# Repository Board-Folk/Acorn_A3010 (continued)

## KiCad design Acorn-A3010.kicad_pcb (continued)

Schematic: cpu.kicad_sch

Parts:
C84: 10uF 16V; CP_Radial_D4.0mm_P2.00mm
C94, C100, C101, C102, C119: 33nF; C_0805_2012Metric; LCSC C344201
C98, C99, C224: 12pF 2%; C_0805_2012Metric; LCSC C1792
C120: 10uF 10V 20%; CP_Radial_Tantal_D7.0mm_P5.00mm
D19: BAS16; SOT-23
IC8: 74HCT14; SOIC-14_3.9x8.7mm_P1.27mm; LCSC C6769
IC12: DS2401+; TO-92_Inline_Wide
IC13: ARM250; PQFP-160_28x28mm_P0.65mm
IC20: 74HC138; SOIC-16_3.9x9.9mm_P1.27mm; LCSC C5602
IC27: 74AC32; SOIC-14_3.9x8.7mm_P1.27mm; LCSC C352943
R3: 22R; R_0805_2012Metric; LCSC C2907244; not fitted
R50, R115, R124, R219: 68R 5% 0.1W; R_0805_2012Metric; LCSC C137498
R83, R84, R85, R86, R87, R89, R91, R102: 4K7 5% 0.1W; R_0805_2012Metric; LCSC C2907326
R88: 1K0 5% 0.1W; R_0805_2012Metric; LCSC C2907326
R94: 100K 5% 0.1W; R_0805_2012Metric; LCSC C149504
R97: 22R 5% 0.1W; R_0805_2012Metric; LCSC C2907244
R104: 1M0 5% 0.1W; R_0805_2012Metric; LCSC C2933280
R110: 47R 5% 0.1W; R_0805_2012Metric; LCSC C137498
R218: 47R 5% 0.1W; R_0805_2012Metric; LCSC C2907268
R223: 220R 5% 0.1W; R_0805_2012Metric; LCSC C17557
R228, R610, R611, R612: 33R 5% 0.1W; R_0805_2012Metric; LCSC C17634
R608: 33R 5% 0.1W; R_0805_2012Metric
RP7: 68Rx8 5%; SOIC-16W_5.3x10.2mm_P1.27mm; LCSC C1739978
RP11: 68Rx8 5%; SOIC-16W_5.3x10.2mm_P1.27mm
TP4: Test; TestPoint_Pad_D1.0mm; not fitted
TP27: compSync; TestPoint_Pad_D1.0mm; not fitted
TP33: ~{EFiq}; TestPoint_Pad_D1.0mm; not fitted
TP34: C2; TestPoint_Pad_D1.0mm; not fitted
TP35: I13; TestPoint_Pad_D1.0mm; not fitted
X4: 72.0MHz; Oscillator_DIP-14
X5: 25.175MHz; Crystal_HC49-4H_Vertical
X100: 40.0MHz; Oscillator_DIP-14; not fitted

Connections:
+5V: C94.1, C100.1, C101.1, C102.1, C119.1, C120.1, D19.3 (K), IC8.14 (VCC), IC13.10 (Vdd), IC13.29 (Vdd), IC13.50 (Vdd), IC13.68 (Vdd), IC13.90 (Vdd), IC13.108 (Vdd), IC13.127 (Vdd), IC13.147 (Vdd), IC20.6 (E3), IC20.16 (VCC), IC27.14 (VCC), R83.2, R84.2, R85.2, R86.2, R87.2, R88.2, R89.1, R91.1, R94.1, R102.2, X4.1 (EN), X4.14 (Vcc), X100.1 (EN), X100.14 (Vcc); also elsewhere on the board
/CPU/Bd0: RP11.1 (R1.1); also elsewhere on the board
/CPU/Bd1: RP11.2 (R2.1); also elsewhere on the board
/CPU/Bd2: RP11.3 (R3.1); also elsewhere on the board
/CPU/Bd3: RP11.4 (R4.1); also elsewhere on the board
/CPU/Bd4: RP11.5 (R5.1); also elsewhere on the board
/CPU/Bd5: RP11.6 (R6.1); also elsewhere on the board
/CPU/Bd6: RP11.7 (R7.1); also elsewhere on the board
/CPU/Bd7: RP11.8 (R8.1); also elsewhere on the board
/CPU/Cas0: IC13.24 (~Cas0); also elsewhere on the board
/CPU/Cas1: IC13.25 (~Cas1); also elsewhere on the board
/CPU/Cas2: IC13.26 (~Cas2); also elsewhere on the board
/CPU/Cas3: IC13.27 (~Cas3); also elsewhere on the board
/CPU/D0: IC13.41 (D0); also elsewhere on the board
/CPU/D1: IC13.42 (D1); also elsewhere on the board
/CPU/D2: IC13.43 (D2); also elsewhere on the board
/CPU/D3: IC13.44 (D3); also elsewhere on the board
/CPU/D4: IC13.45 (D4); also elsewhere on the board
/CPU/D5: IC13.46 (D5); also elsewhere on the board
/CPU/D6: IC13.47 (D6); also elsewhere on the board
/CPU/D7: IC13.48 (D7); also elsewhere on the board
/CPU/D8: IC13.51 (D8); also elsewhere on the board
/CPU/D9: IC13.52 (D9); also elsewhere on the board
/CPU/D10: IC13.53 (D10); also elsewhere on the board
/CPU/D11: IC13.54 (D11); also elsewhere on the board
/CPU/D12: IC13.55 (D12); also elsewhere on the board
/CPU/D13: IC13.56 (D13); also elsewhere on the board
/CPU/D14: IC13.57 (D14); also elsewhere on the board
/CPU/D15: IC13.58 (D15); also elsewhere on the board
/CPU/D16: IC13.59 (D16); also elsewhere on the board
/CPU/D17: IC13.60 (D17); also elsewhere on the board
/CPU/D18: IC13.61 (D18); also elsewhere on the board
/CPU/D19: IC13.62 (D19); also elsewhere on the board
/CPU/D20: IC13.63 (D20); also elsewhere on the board
/CPU/D21: IC13.64 (D21); also elsewhere on the board
/CPU/D22: IC13.65 (D22); also elsewhere on the board
/CPU/D23: IC13.66 (D23); also elsewhere on the board
/CPU/D24: IC13.69 (D24); also elsewhere on the board
/CPU/D25: IC13.70 (D25); also elsewhere on the board
/CPU/D26: IC13.71 (D26); also elsewhere on the board
/CPU/D27: IC13.72 (D27); also elsewhere on the board
/CPU/D28: IC13.73 (D28); also elsewhere on the board
/CPU/D29: IC13.74 (D29); also elsewhere on the board
/CPU/D30: IC13.75 (D30); also elsewhere on the board
/CPU/D31: IC13.76 (D31); also elsewhere on the board
/CPU/La2: IC13.79 (La2); also elsewhere on the board
/CPU/La3: IC13.80 (La3); also elsewhere on the board
/CPU/La4: IC13.81 (La4); also elsewhere on the board
/CPU/La5: IC13.82 (La5); also elsewhere on the board
/CPU/La6: IC13.83 (La6); also elsewhere on the board
/CPU/La7: IC13.84 (La7); also elsewhere on the board
/CPU/La8: IC13.85 (La8); also elsewhere on the board
/CPU/La9: IC13.86 (La9); also elsewhere on the board
/CPU/La10: IC13.87 (La10); also elsewhere on the board
/CPU/La11: IC13.88 (La11); also elsewhere on the board
/CPU/La12: IC13.91 (La12); also elsewhere on the board
/CPU/La13: IC13.92 (La13); also elsewhere on the board
/CPU/La14: IC13.93 (La14), IC20.1 (A0); also elsewhere on the board
/CPU/La15: IC13.94 (La15), IC20.2 (A1); also elsewhere on the board
/CPU/La16: IC13.95 (La16), IC20.3 (A2); also elsewhere on the board
/CPU/La17: IC13.96 (La17), IC20.4 (E1); also elsewhere on the board
/CPU/La18: IC13.97 (La18); also elsewhere on the board
/CPU/La19: IC13.98 (La19); also elsewhere on the board
/CPU/La20: IC13.99 (La20); also elsewhere on the board
/CPU/La21: IC13.100 (La21), IC20.5 (E2); also elsewhere on the board
/CPU/Ra0: RP7.9 (R8.2); also elsewhere on the board
/CPU/Ra1: RP7.10 (R7.2); also elsewhere on the board
/CPU/Ra2: RP7.11 (R6.2); also elsewhere on the board
/CPU/Ra3: RP7.12 (R5.2); also elsewhere on the board
/CPU/Ra4: RP7.13 (R4.2); also elsewhere on the board
/CPU/Ra5: RP7.14 (R3.2); also elsewhere on the board
/CPU/Ra6: RP7.15 (R2.2); also elsewhere on the board
/CPU/Ra7: RP7.16 (R1.2); also elsewhere on the board
/CPU/Ra8: R124.2; also elsewhere on the board
/CPU/Ra9: R115.2; also elsewhere on the board
Aen: IC13.102 (Aen); also elsewhere on the board
B: IC13.120 (Bout); also elsewhere on the board
C0: IC13.136 (C0); also elsewhere on the board
C1: IC13.137 (C1); also elsewhere on the board
CLK2: R218.2; also elsewhere on the board
Clkvid: IC13.124 (Clkvid); also elsewhere on the board
Dbe: IC13.40 (Dbe); also elsewhere on the board
Drq: IC13.129 (Drq); also elsewhere on the board
G: IC13.119 (Gout); also elsewhere on the board
GND: C84.2, C94.2, C98.2, C99.2, C100.2, C101.2, C102.2, C119.2, C120.2, C224.2, IC8.7 (GND), IC12.1 (GND), IC13.9 (Vss), IC13.18 (Vss), IC13.28 (Vss), IC13.49 (Vss), IC13.67 (Vss), IC13.89 (Vss), IC13.107 (Vss), IC13.126 (Vss), IC13.146 (Vss), IC20.8 (GND), IC27.4, IC27.5, IC27.7 (GND), IC27.9, IC27.10, IC27.12, IC27.13, X4.7 (GND), X100.7 (GND); also elsewhere on the board
HS: IC13.19 (Eorh); also elsewhere on the board
ID0: IC13.13 (Mid0); also elsewhere on the board
ID1: IC13.14 (Mid1); also elsewhere on the board
ID2: IC13.15 (Mid2); also elsewhere on the board
ID3: IC13.16 (Mid3); also elsewhere on the board
Kin: IC13.2 (Kin); also elsewhere on the board
Kout: IC13.3 (Kout); also elsewhere on the board
Left+: IC13.112 (Lch); also elsewhere on the board
Left-: IC13.113 (Lch-); also elsewhere on the board
unnamed: C224.1, IC27.1, R223.1
unnamed: C84.1, D19.1 (A), IC13.7 (~Por), R94.2
unnamed: IC12.2 (DQ), IC13.139 (C3), R89.2
unnamed: IC13.148 (Bd0), RP11.16 (R1.2)
unnamed: IC13.149 (Bd1), RP11.15 (R2.2)
unnamed: IC13.150 (Bd2), RP11.14 (R3.2)
unnamed: IC13.151 (Bd3), RP11.13 (R4.2)
unnamed: IC13.152 (Bd4), RP11.12 (R5.2)
unnamed: IC13.153 (Bd5), RP11.11 (R6.2)
unnamed: IC13.154 (Bd6), RP11.10 (R7.2)
unnamed: IC13.155 (Bd7), RP11.9 (R8.2)
unnamed: IC13.138 (C2), R88.1, TP34.1
unnamed: IC13.135 (Clk2), R218.1
unnamed: C99.1, IC13.12 (Clk25in), R104.1, X5.1
unnamed: C98.1, IC13.11 (Clk25out), R104.2, X5.2
unnamed: IC13.4 (Clk72), R97.1
unnamed: IC13.17 (Clkkb), R50.1
unnamed: IC13.30 (Ra0), RP7.8 (R8.1)
unnamed: IC13.31 (Ra1), RP7.7 (R7.1)
unnamed: IC13.32 (Ra2), RP7.6 (R6.1)
unnamed: IC13.33 (Ra3), RP7.5 (R5.1)
unnamed: IC13.34 (Ra4), RP7.4 (R4.1)
unnamed: IC13.35 (Ra5), RP7.3 (R3.1)
unnamed: IC13.36 (Ra6), RP7.2 (R2.1)
unnamed: IC13.37 (Ra7), RP7.1 (R1.1)
unnamed: IC13.38 (Ra8), R124.1
unnamed: IC13.39 (Ra9), R115.1
unnamed: IC13.8 (Sysclk), R3.1
unnamed: IC13.156 (Wbe), R608.1
unnamed: IC13.141 (~Iogt), R228.2
unnamed: IC13.140 (~Iorq), IC27.2, R223.2
unnamed: IC13.157 (~Rbe), R610.2
unnamed: IC13.5 (~Test), TP4.1
unnamed: IC13.158 (~Wbl), R611.2
unnamed: IC27.3, R219.2
unnamed: R97.2, X4.8 (OUT)
unnamed: R3.2, X100.8 (OUT)
Pr/Nw: IC13.78 (Pr/nw); also elsewhere on the board
R: IC13.118 (Rout); also elsewhere on the board
Ref8M: IC13.145 (Ioclk); also elsewhere on the board
Right+: IC13.114 (Rch); also elsewhere on the board
Right-: IC13.115 (Rch-); also elsewhere on the board
Rst: IC8.8; also elsewhere on the board
SndRef: IC13.109 (Rsdac); also elsewhere on the board
SndVDD: IC13.111 (Sndvdd); also elsewhere on the board
SndVSS: IC13.110 (Sndvss); also elsewhere on the board
Tc: IC13.106 (Tc); also elsewhere on the board
VidRef: IC13.116 (Rvdac); also elsewhere on the board
Vidclk: IC13.123 (Vidclk); also elsewhere on the board
Vidvss: IC13.117 (Vidvss); also elsewhere on the board
V/CS: IC13.20 (Eorv); also elsewhere on the board
clkkb: R50.2; also elsewhere on the board
compsync: IC13.125 (Csync), TP27.1
sink: IC13.121 (Sink); also elsewhere on the board
~Bl: R612.1; also elsewhere on the board
~Dack: IC13.105 (~Dack); also elsewhere on the board
~EFiq: IC13.134 (Efiq), R87.1, TP33.1; also elsewhere on the board
~Fintr: IC13.132 (~Fintr), R85.1; also elsewhere on the board
~I13: IC13.143 (~I13), R91.2, TP35.1; also elsewhere on the board
~Index: IC13.128 (~Index); also elsewhere on the board
~Iogt: R228.1; also elsewhere on the board
~Iorq: R219.1; also elsewhere on the board
~Ior: IC13.103 (~Ior); also elsewhere on the board
~Iow: IC13.104 (~Iow); also elsewhere on the board
~Joyst1: IC13.21 (~Joy1); also elsewhere on the board
~Joyst2: IC13.22 (~Joy2); also elsewhere on the board
~Mcras: IC13.23 (~Ras), R110.1
~Ms1: IC20.14 (O1); also elsewhere on the board
~Pfiq: IC13.131 (~Pfiq), R84.1; also elsewhere on the board
~Pint: IC13.101 (~Pintr), R102.1; also elsewhere on the board
~Pirq: IC13.130 (~Pirq), R83.1; also elsewhere on the board
~Pre: IC13.1 (~Re); also elsewhere on the board
~Ps1: IC13.142 (~Ps1); also elsewhere on the board
~Pwe: IC13.160 (~We); also elsewhere on the board
~Ras: R110.2; also elsewhere on the board
~Rbe: R610.1; also elsewhere on the board
~Rbl: IC13.159 (~Rbl), R612.2; also elsewhere on the board
~Romcs: IC13.77 (~Romcs); also elsewhere on the board
~Rst: IC8.9, IC13.6 (~Rst); also elsewhere on the board
~S2: IC13.144 (S2); also elsewhere on the board
~Sintr: IC13.133 (~Sintr), R86.1; also elsewhere on the board
~Sup: IC13.122 (~Sup); also elsewhere on the board
~Wbe: R608.2; also elsewhere on the board
~Wbl: R611.1; also elsewhere on the board

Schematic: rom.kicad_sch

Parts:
C121, C130: 33nF; C_0805_2012Metric; LCSC C344201
C140: 33nF; C_0805_2012Metric; LCSC C49678
IC17: 0296,061; DIP-42_W15.24mm
IC18: 0296,062; DIP-42_W15.24mm
LK16: Conn_01x06; PinHeader_1x06_P2.54mm_Vertical
R113: 22R 5% 0.1W; R_0805_2012Metric; LCSC C2907244
R114: 330R 5% 0.1W; R_0805_2012Metric; LCSC C17630

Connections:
+5V: C121.1, C130.1, C140.2, IC17.22 (Vcc), IC17.32 (BHE), IC18.22 (Vcc), IC18.32 (BHE), LK16.1; also elsewhere on the board
/CPU/D0: IC17.14 (D0), LK16.2; also elsewhere on the board
/CPU/D1: IC17.16 (D1); also elsewhere on the board
/CPU/D2: IC17.18 (D2); also elsewhere on the board
/CPU/D3: IC17.20 (D3); also elsewhere on the board
/CPU/D4: IC17.23 (D4); also elsewhere on the board
/CPU/D5: IC17.25 (D5); also elsewhere on the board
/CPU/D6: IC17.27 (D6); also elsewhere on the board
/CPU/D7: IC17.29 (D7); also elsewhere on the board
/CPU/D8: IC17.15 (D8); also elsewhere on the board
/CPU/D9: IC17.17 (D9); also elsewhere on the board
/CPU/D10: IC17.19 (D10); also elsewhere on the board
/CPU/D11: IC17.21 (D11); also elsewhere on the board
/CPU/D12: IC17.24 (D12); also elsewhere on the board
/CPU/D13: IC17.26 (D13); also elsewhere on the board
/CPU/D14: IC17.28 (D14); also elsewhere on the board
/CPU/D15: IC17.30 (D15); also elsewhere on the board
/CPU/D16: IC18.14 (D0); also elsewhere on the board
/CPU/D17: IC18.16 (D1); also elsewhere on the board
/CPU/D18: IC18.18 (D2); also elsewhere on the board
/CPU/D19: IC18.20 (D3); also elsewhere on the board
/CPU/D20: IC18.23 (D4); also elsewhere on the board
/CPU/D21: IC18.25 (D5); also elsewhere on the board
/CPU/D22: IC18.27 (D6); also elsewhere on the board
/CPU/D23: IC18.29 (D7); also elsewhere on the board
/CPU/D24: IC18.15 (D8); also elsewhere on the board
/CPU/D25: IC18.17 (D9); also elsewhere on the board
/CPU/D26: IC18.19 (D10); also elsewhere on the board
/CPU/D27: IC18.21 (D11); also elsewhere on the board
/CPU/D28: IC18.24 (D12); also elsewhere on the board
/CPU/D29: IC18.26 (D13); also elsewhere on the board
/CPU/D30: IC18.28 (D14); also elsewhere on the board
/CPU/D31: IC18.30 (D15); also elsewhere on the board
/CPU/La2: IC17.10 (A0), IC18.10 (A0); also elsewhere on the board
/CPU/La3: IC17.9 (A1), IC18.9 (A1); also elsewhere on the board
/CPU/La4: IC17.8 (A2), IC18.8 (A2); also elsewhere on the board
/CPU/La5: IC17.7 (A3), IC18.7 (A3); also elsewhere on the board
/CPU/La6: IC17.6 (A4), IC18.6 (A4); also elsewhere on the board
/CPU/La7: IC17.5 (A5), IC18.5 (A5); also elsewhere on the board
/CPU/La8: IC17.4 (A6), IC18.4 (A6); also elsewhere on the board
/CPU/La9: IC17.3 (A7), IC18.3 (A7); also elsewhere on the board
/CPU/La10: IC17.41 (A8), IC18.41 (A8); also elsewhere on the board
/CPU/La11: IC17.40 (A9), IC18.40 (A9); also elsewhere on the board
/CPU/La12: IC17.39 (A10), IC18.39 (A10); also elsewhere on the board
/CPU/La13: IC17.38 (A11), IC18.38 (A11); also elsewhere on the board
/CPU/La14: IC17.37 (A12), IC18.37 (A12); also elsewhere on the board
/CPU/La15: IC17.36 (A13), IC18.36 (A13); also elsewhere on the board
/CPU/La16: IC17.35 (A14), IC18.35 (A14); also elsewhere on the board
/CPU/La17: IC17.34 (A15), IC18.34 (A15); also elsewhere on the board
/CPU/La18: IC17.33 (A16), IC18.33 (A16); also elsewhere on the board
/CPU/La19: IC17.2 (A17), IC18.2 (A17); also elsewhere on the board
/CPU/La20: IC17.1 (A18), IC18.1 (A18); also elsewhere on the board
/CPU/La21: IC17.42 (NC/A21), IC18.42 (NC/A21), LK16.3; also elsewhere on the board
GND: C121.2, C130.2, C140.1, IC17.12 (Vss), IC17.31 (Vss), IC18.12 (Vss), IC18.31 (Vss), LK16.6, R114.1; also elsewhere on the board
unnamed: IC17.11 (~CE), IC18.11 (~CE), R113.2
testak: IC17.13 (~OE), IC18.13 (~OE), LK16.4, R114.2
~Romcs: R113.1; also elsewhere on the board
~Rst: LK16.5; also elsewhere on the board

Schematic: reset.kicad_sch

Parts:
C1: 10uF 16V; CP_Radial_D5.0mm_P2.50mm
CX1: 47pF; C_Axial_L5.1mm_D3.1mm_P12.50mm_Horizontal
IC8: 74HCT14; SOIC-14_3.9x8.7mm_P1.27mm; LCSC C6769
Q3: BC849; SOT-23; LCSC C49238181
R1: 22K 5% 0.1W; R_0805_2012Metric; LCSC C17560
R2: 100R 5% 0.1W; R_0805_2012Metric; LCSC C17408
R16, R17: 2K2 5% 0.1W; R_0805_2012Metric; LCSC C17520
R18: 1K2 5% 0.1W; R_0805_2012Metric; LCSC C2933293
SW1: SW_Push_DPDT; Reset_Switch
TP7: RESET; TestPoint_Pad_D1.0mm; not fitted

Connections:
+5V: R1.1, R18.1; also elsewhere on the board
GND: C1.2, CX1.1, Q3.2 (E), R17.2, SW1.3 (C); also elsewhere on the board
unnamed: C1.1, IC8.11, R1.2, R2.2, TP7.1
unnamed: IC8.10, R16.1
unnamed: Q3.1 (B), R16.2, R17.1
~Reset: R2.1, SW1.2 (B); also elsewhere on the board
~Rst: CX1.2, Q3.3 (C), R18.2; also elsewhere on the board

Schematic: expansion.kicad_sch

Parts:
R90, R92: 1K2 5% 0.1W; R_0805_2012Metric; LCSC C2933293
R217, R221, R227: 33R 5% 0.1W; R_0805_2012Metric; LCSC C17634
R220: 47R 5% 0.1W; R_0805_2012Metric; LCSC C2907268
R222: 68R 5% 0.1W; R_0805_2012Metric; LCSC C137498
SK5, SK9: Conn_01x17_Socket; PinSocket_1x17_P2.54mm_Vertical
SK7, SK8: Conn_01x05_Socket; PinSocket_1x05_P2.54mm_Vertical

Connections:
+5V: R90.1, R92.2, SK5.1, SK5.17, SK8.5, SK9.2; also elsewhere on the board
/CPU/Bd0: SK5.7; also elsewhere on the board
/CPU/Bd1: SK5.8; also elsewhere on the board
/CPU/Bd2: SK5.9; also elsewhere on the board
/CPU/Bd3: SK5.10; also elsewhere on the board
/CPU/Bd4: SK5.11; also elsewhere on the board
/CPU/Bd5: SK5.12; also elsewhere on the board
/CPU/Bd6: SK5.13; also elsewhere on the board
/CPU/Bd7: SK5.14; also elsewhere on the board
/CPU/La2: SK5.5; also elsewhere on the board
/CPU/La3: SK5.6; also elsewhere on the board
/CPU/La4: SK9.5; also elsewhere on the board
/CPU/La5: SK9.6; also elsewhere on the board
/CPU/La6: SK9.7; also elsewhere on the board
/CPU/La7: SK9.8; also elsewhere on the board
/CPU/La8: SK9.10; also elsewhere on the board
/CPU/La9: SK9.11; also elsewhere on the board
/CPU/La10: SK9.12; also elsewhere on the board
/CPU/La11: SK9.13; also elsewhere on the board
/CPU/La12: SK9.14; also elsewhere on the board
/CPU/La13: SK9.15; also elsewhere on the board
C0: SK7.1; also elsewhere on the board
C1: SK7.2; also elsewhere on the board
CLK2: SK5.4; also elsewhere on the board
GND: SK5.16, SK8.1, SK9.1, SK9.9, SK9.17; also elsewhere on the board
unnamed: R221.2, SK5.2
unnamed: R220.2, SK5.3
unnamed: R92.1, R227.2, SK7.3
unnamed: R222.2, SK8.2
unnamed: R217.2, SK9.3
Pr/Nw: SK9.4; also elsewhere on the board
Ref8M: R222.1; also elsewhere on the board
~Iogt: R90.2, SK7.5; also elsewhere on the board
~Iorq: SK7.4; also elsewhere on the board
~Ms1: SK8.4; also elsewhere on the board
~Pfiq: SK8.3; also elsewhere on the board
~Pirq: SK9.16; also elsewhere on the board
~Pre: R217.1; also elsewhere on the board
~Ps1: R220.1; also elsewhere on the board
~Pwe: R221.1; also elsewhere on the board
~Rbl: R227.1; also elsewhere on the board
~Rst: SK5.15; also elsewhere on the board

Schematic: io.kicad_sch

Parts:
C15, C148: 4.7nF; C_Rect_L7.0mm_W2.5mm_P5.00mm
C75: 68pF; C_0805_2012Metric
C108, C111, C112, C113, C114, C115, C122, C123, C125, C126, C132, C134, C136, C153, C154, C155, C156: 100pF 2%; C_0805_2012Metric; LCSC C1790
C127, C133, C135, C141, C142, C143, C144, C145: 1nF 10%; C_0805_2012Metric; LCSC C46653
C128, C129: 22pF 2%; C_0805_2012Metric; LCSC C1804
C137, C146: 33nF; C_0805_2012Metric; LCSC C344201
C139: 10uF; CP_Radial_Tantal_D9.0mm_P5.00mm
C147, C158: 100nF 20%; C_0805_2012Metric; LCSC C49678
C149: 2.7nF 5%; C_0805_2012Metric; LCSC C2987938
C150: 150nF 5%; C_Rect_L7.0mm_W2.5mm_P5.00mm
C157: 47uF 16V; CP_Radial_D8.0mm_P5.00mm
D21: BAT; SOT-23-3
IC16, IC23: MC1489; SOIC-14_3.9x8.7mm_P1.27mm; LCSC C3199481
IC19: MC1488; SOIC-14_3.9x8.7mm_P1.27mm; LCSC C3213152
IC24: 82C711 SIO; PQFP-100_14x20mm_P0.65mm
L14: 1A 80R@100MHz; L_Acorn_8x3mm
LK11: NF; Link_Connected
LK18: Pren; PinHeader_1x02_P2.54mm_Vertical
PL8: Serial; DSUB-9_Male_Horizontal_P2.77x2.84mm_EdgePinOffset9.90mm_Hou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
PL9: IDC34 Box FDD; IDC-Header_2x17_P2.54mm_Vertical
R67: 82R; R_0805_2012Metric
R116, R117, R118, R121, R122, R123, R126, R131: 4K7 5% 0.1W; R_0805_2012Metric; LCSC C2907326
R119: 10K 5% 0.1W; R_0805_2012Metric; LCSC C2907219
R120: 33R 5% 0.1W; R_0805_2012Metric; LCSC C17634
R127: 6K81 1% 0.25W; R_1206_3216Metric; LCSC C5713328
R128: 18K2 1% 0.25W; R_1206_3216Metric; LCSC C2090916
R129: 1K2 5% 0.1W; R_0805_2012Metric; LCSC C2933293
R138, R140, R141: 4K7 5% 0.1W; R_0805_2012Metric; LCSC C2907326; not fitted
R139, R142, R143, R144, R145: 1K 5% 0.1W; R_0805_2012Metric; LCSC C2907232
R215: 0R 0.1W; R_0805_2012Metric; LCSC C17477
RP8, RP9: 33Rx8 5%; SOIC-16W_5.3x10.2mm_P1.27mm; LCSC C1739831
SK10: Printer; DSUB-25_Female_Horizontal_P2.77x2.84mm_EdgePinOffset9.90mm_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
TP5: Filter; TestPoint_Pad_D1.0mm; not fitted
TP8: PwrGd; TestPoint_Pad_D1.0mm; not fitted
TP9: SetCur; TestPoint_Pad_D1.0mm; not fitted
TP10: RVI; TestPoint_Pad_D1.0mm; not fitted
TP11: AVcc; TestPoint_Pad_D1.0mm; not fitted
X7: 24MHz; Crystal_HC49-U_Horizontal_1EP_style2

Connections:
+5C: C146.1, C157.1, IC16.14 (VCC), IC23.14 (VCC), R116.2, R117.2, R118.2, R121.2, R126.2, R131.2; also elsewhere on the board
+5V: C137.1, C139.1, C158.1, IC24.15, IC24.72, L14.2, R119.1, R122.2, R123.2, R138.2, R139.2, R140.2, R141.2, R142.2, R143.2, R144.2, R145.2; also elsewhere on the board
+12V: IC19.14 (VCC); also elsewhere on the board
-12V: IC19.1 (VEE); also elsewhere on the board
/CPU/Bd0: IC24.48 (D0); also elsewhere on the board
/CPU/Bd1: IC24.49 (D1); also elsewhere on the board
/CPU/Bd2: IC24.50 (D2); also elsewhere on the board
/CPU/Bd3: IC24.51 (D3); also elsewhere on the board
/CPU/Bd4: IC24.53 (D4); also elsewhere on the board
/CPU/Bd5: IC24.54 (D5); also elsewhere on the board
/CPU/Bd6: IC24.55 (D6); also elsewhere on the board
/CPU/Bd7: IC24.56 (D7); also elsewhere on the board
/CPU/La2: IC24.28 (A0); also elsewhere on the board
/CPU/La3: IC24.29 (A1); also elsewhere on the board
/CPU/La4: IC24.30 (A2); also elsewhere on the board
/CPU/La5: IC24.31 (A3); also elsewhere on the board
/CPU/La6: IC24.32 (A4); also elsewhere on the board
/CPU/La7: IC24.33 (A5); also elsewhere on the board
/CPU/La8: IC24.34 (A6); also elsewhere on the board
/CPU/La9: IC24.41 (A7); also elsewhere on the board
/CPU/La10: IC24.42 (A8); also elsewhere on the board
/CPU/La11: IC24.43 (A9); also elsewhere on the board
/IO/DC: IC24.17 (Dskchg), PL9.34, R145.1
/IO/Density: IC24.1 (Rpm/Lc), PL9.2, R138.1
/IO/~Dirin: IC24.7 (Dir), PL9.18
/IO/~MotorOn: IC24.2 (Mtr0), PL9.16, R141.1
/IO/~Readdata: IC24.16 (Rddata), PL9.30, R144.1
/IO/~Side1: IC24.11 (Hdsel), PL9.32
/IO/~Step: IC24.8 (Step), PL9.20
/IO/~Track00: IC24.13 (Trk0), PL9.26, R142.1
/IO/~Writedata: IC24.9 (Wrdata), PL9.22
/IO/~Writegate: IC24.10 (Wgate), PL9.24
/IO/~Writeprot: IC24.14 (Wrprt), PL9.28, R143.1
Aen: IC24.46 (Aen); also elsewhere on the board
Drq: IC24.52 (Fdrq); also elsewhere on the board
GND: C75.1, C108.2, C111.2, C112.2, C113.2, C114.2, C115.2, C122.2, C123.2, C125.2, C126.2, C127.2, C128.2, C129.2, C132.2, C133.2, C134.2, C135.2, C136.2, C137.2, C139.2, C141.2, C142.2, C143.2, C144.2, C145.2, C146.2, C147.2, C153.2, C154.2, C155.2, C156.2, C157.2, C158.2, D21.1 (A), IC16.4 (InputB), IC16.7 (GND), IC19.2 (InputA), IC19.7 (GND), IC23.7 (GND), IC23.10 (InputC), IC23.13 (InputD), IC24.6, IC24.47, IC24.67, LK11.2, LK18.1, PL8.0 (PAD), PL8.5, PL9.3, PL9.5, PL9.7, PL9.9, PL9.11, PL9.13, PL9.15, PL9.17, PL9.19, PL9.21, PL9.23, PL9.25, PL9.27, PL9.29, PL9.31, PL9.33, SK10.0, SK10.18, SK10.19, SK10.20, SK10.21, SK10.22, SK10.23, SK10.24, SK10.25, X7.3; also elsewhere on the board
Ided7: IC24.22 (Ided7); also elsewhere on the board
unnamed: C128.1, R215.2, X7.2
unnamed: C136.1, R120.2, R121.1, SK10.17
unnamed: C15.2, C148.1, C150.2, R129.1
unnamed: C122.1, IC16.1 (InputA), PL8.6
unnamed: IC16.3 (OutputA), IC24.80 (Dsr1)
unnamed: C108.1, IC16.10 (InputC), PL8.9
unnamed: IC16.8 (OutputC), IC24.84 (Ri1)
unnamed: C112.1, IC16.13 (InputD), PL8.8
unnamed: IC16.11 (OutputD), IC24.82 (Cts1)
unnamed: IC19.5 (InputB2), IC24.79 (Txd1)
unnamed: C113.1, IC19.6 (OutputB), PL8.3
unnamed: IC19.9 (InputC2), IC24.83 (Dtr1)
unnamed: C111.1, IC19.8 (OutputC), PL8.4
unnamed: IC19.12 (InputD2), IC24.81 (Rts1)
unnamed: C114.1, IC19.11 (OutputD), PL8.7
unnamed: C123.1, IC23.1 (InputA), PL8.1
unnamed: IC23.3 (OutputA), IC24.85 (Dcd1)
unnamed: C115.1, IC23.4 (InputB), PL8.2
unnamed: IC23.6 (OutputB), IC24.78 (Rxd1)
unnamed: IC24.62 (Ack), RP8.13 (R4.2)
unnamed: IC24.76 (Autofd), RP9.10 (R7.2)
unnamed: C147.1, IC24.100 (Avcc), L14.1, TP11.1
unnamed: C148.2, C149.2, IC24.98 (Avss), LK11.1, R127.2, R128.2
unnamed: IC24.61 (Busy), RP8.14 (R3.2)
unnamed: IC24.19 (Drvtyp), R122.1
unnamed: IC24.75 (Error), RP9.13 (R4.2)
unnamed: C150.1, IC24.95 (Fgnd250)
unnamed: C15.1, IC24.94 (Fgnd500)
unnamed: C149.1, IC24.96 (Filter), R129.2, TP5.1
unnamed: IC24.74 (Init), RP9.9 (R8.2)
unnamed: IC24.21 (Osc2), R215.1
unnamed: C129.1, IC24.20 (Oscl/Clk), X7.1
unnamed: IC24.71 (Pd0), RP9.12 (R5.2)
unnamed: IC24.70 (Pd1), RP9.14 (R3.2)
unnamed: IC24.69 (Pd2), RP9.15 (R2.2)
unnamed: IC24.68 (Pd3), RP9.16 (R1.2)
unnamed: IC24.66 (Pd4), RP8.9 (R8.2)
unnamed: IC24.65 (Pd5), RP8.10 (R7.2)
unnamed: IC24.64 (Pd6), RP8.11 (R6.2)
unnamed: IC24.63 (Pd7), RP8.12 (R5.2)
unnamed: IC24.60 (Pe), RP8.15 (R2.2)
unnamed: IC24.18 (Pren), LK18.2, R123.1
unnamed: IC24.58 (Pwrgd), R119.2, TP8.1
unnamed: IC24.97 (Rvi), R128.1, TP10.1
unnamed: IC24.99 (Setcur), R127.1, TP9.1
unnamed: IC24.59 (Slct), RP8.16 (R1.2)
unnamed: IC24.73 (Slctin), R120.1
unnamed: IC24.77 (Strobe), RP9.11 (R6.2)
unnamed: PL9.8, R67.2, R139.1
unnamed: C156.1, RP8.1 (R1.1), SK10.13
unnamed: C155.1, RP8.2 (R2.1), SK10.12
unnamed: C154.1, R131.1, RP8.3 (R3.1), SK10.11
unnamed: C153.1, R126.1, RP8.4 (R4.1), SK10.10
unnamed: C145.1, RP8.5 (R5.1), SK10.9
unnamed: C144.1, RP8.6 (R6.1), SK10.8
unnamed: C143.1, RP8.7 (R7.1), SK10.7
unnamed: C142.1, RP8.8 (R8.1), SK10.6
unnamed: C141.1, RP9.1 (R1.1), SK10.5
unnamed: C135.1, RP9.2 (R2.1), SK10.4
unnamed: C133.1, RP9.3 (R3.1), SK10.3
unnamed: C132.1, RP9.4 (R4.1), SK10.15
unnamed: C127.1, RP9.5 (R5.1), SK10.2
unnamed: C125.1, R116.1, RP9.6 (R6.1), SK10.1
unnamed: C126.1, R117.1, RP9.7 (R7.1), SK10.14
unnamed: C134.1, R118.1, RP9.8 (R8.1), SK10.16
Rst: IC24.57 (Rst); also elsewhere on the board
Tc: IC24.35 (Tc); also elsewhere on the board
~Dack: IC24.36 (Dack); also elsewhere on the board
~Fintr: IC24.40 (Fintr); also elsewhere on the board
~Hdsc0: IC24.25 (Hdcs0); also elsewhere on the board
~Hdsc1: IC24.26 (Hdcs1); also elsewhere on the board
~Index: C75.2, D21.3 (K), IC24.12 (Index), R67.1; also elsewhere on the board
~Iocs: IC24.27 (Iocsl6); also elsewhere on the board
~Ior: IC24.44 (Ior); also elsewhere on the board
~Iow: IC24.45 (Iow); also elsewhere on the board
~Pint: IC24.39 (Pintr); also elsewhere on the board
~Sel0: IC24.4 (Drv0), PL9.10, R140.1; also elsewhere on the board
~Sintr: IC24.38 (Irq4); also elsewhere on the board

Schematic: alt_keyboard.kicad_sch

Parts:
C3: 47nF 20%; C_0805_2012Metric; LCSC C107154
IC8: 74HCT14; SOIC-14_3.9x8.7mm_P1.27mm; LCSC C6769
LK3: Conn_01x06; PinHeader_1x06_P2.54mm_Vertical
LK14: Conn_01x03; PinHeader_1x03_P2.54mm_Vertical
R62: 10K 5% 0.1W; R_0805_2012Metric; LCSC C2907219
R63: 220R 5% 0.1W; R_0805_2012Metric; LCSC C17557
R213: 2K2 5% 0.1W; R_0805_2012Metric; LCSC C17520

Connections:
+5V: C3.1, LK3.4; also elsewhere on the board
GND: C3.2, LK3.3, R62.1; also elsewhere on the board
Kbkin: LK14.1; also elsewhere on the board
Kin: LK14.2; also elsewhere on the board
Kout: IC8.13; also elsewhere on the board
unnamed: IC8.1, R62.2, R213.1
unnamed: IC8.12, R63.1
unnamed: LK3.5, R213.2
unnamed: LK3.6, R63.2
unnamed: IC8.2, LK14.3
~Reset: LK3.1; also elsewhere on the board

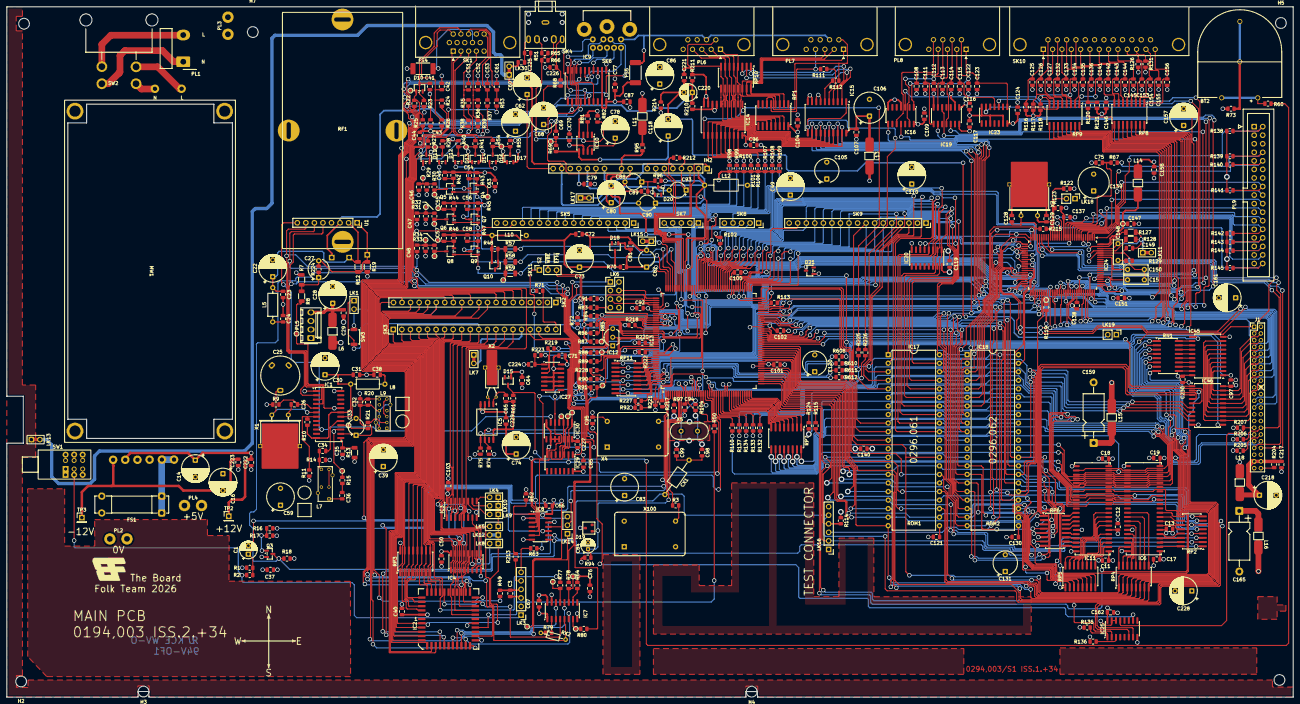
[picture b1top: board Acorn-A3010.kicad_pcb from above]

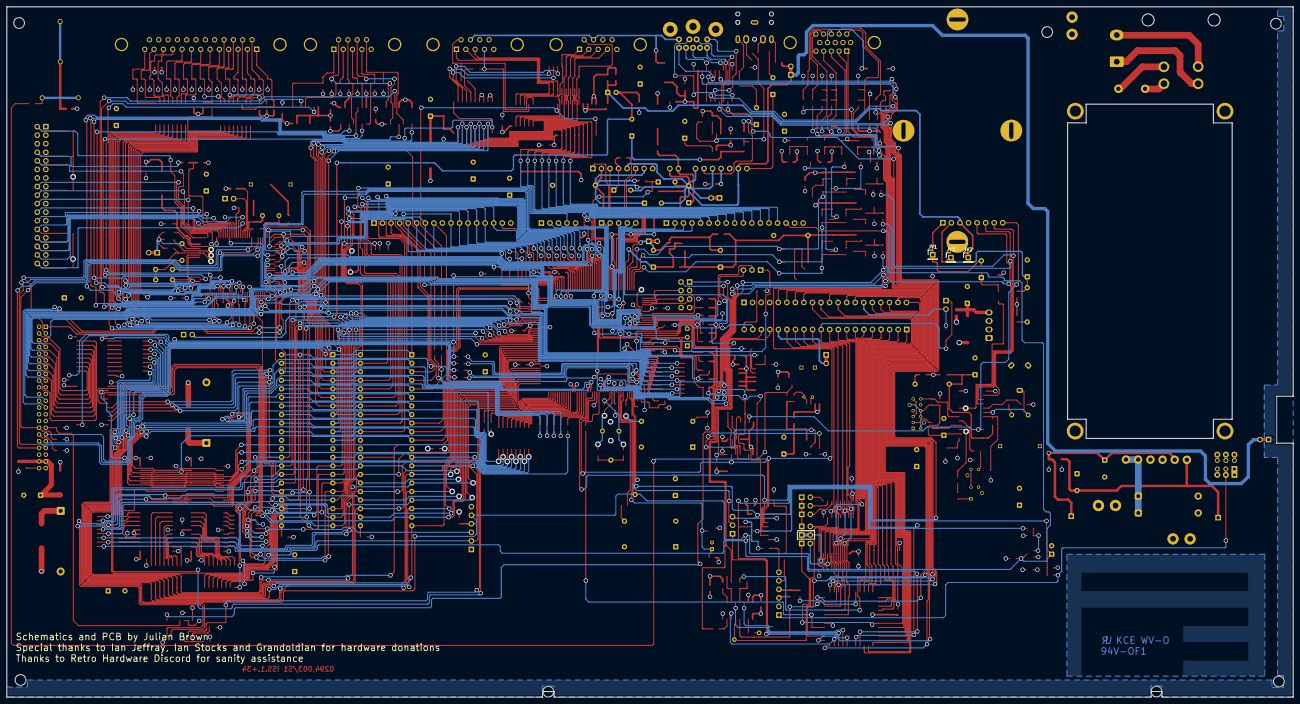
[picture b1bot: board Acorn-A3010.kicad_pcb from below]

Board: 4 copper layers, 382.0 x 205.0 mm, 505 parts (10 on the bottom side), 524 nets.

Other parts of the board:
Ge: LOGO; BoardFolk

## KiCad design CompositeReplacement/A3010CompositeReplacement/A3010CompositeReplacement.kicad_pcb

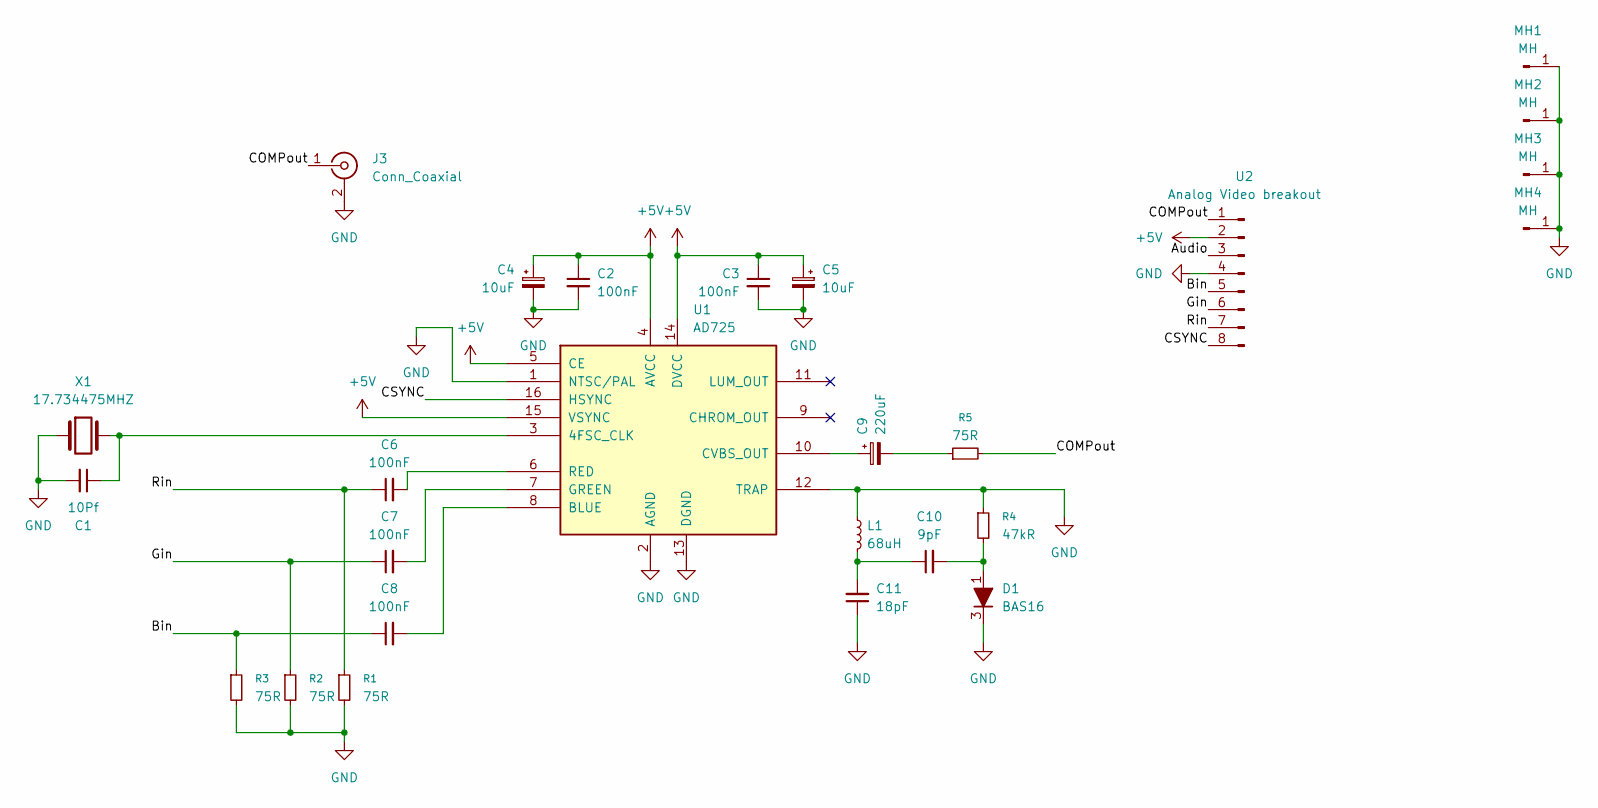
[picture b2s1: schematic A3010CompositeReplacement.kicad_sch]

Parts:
C1: 10Pf; C_0805_2012Metric
C2, C3, C6, C7, C8: 100nF; C_0805_2012Metric
C4, C5: 10uF; CP_EIA-3216-18_Kemet-A; DigiKey 478-11220-1-ND
C9: 220uF; CP_EIA-3216-18_Kemet-A; DigiKey 478-4922-1-ND
C10: 9pF; C_0805_2012Metric
C11: 18pF; C_0805_2012Metric
D1: BAS16; SOT-23
J3: Conn_Coaxial; CUI_RCJ-014-SMT
L1: 68uH; L_0805_2012Metric; DigiKey 445-1069-1-ND
MH1, MH2, MH3, MH4: MH; PinHeader_1x01_P2.54mm_Vertical
R1, R2, R3, R5: 75R; R_0805_2012Metric
R4: 47kR; R_0805_2012Metric
U1: AD725; SOIC-16W_7.5x10.3mm_P1.27mm
U2: Analog Video breakout; PinHeader_1x08_P2.54mm_Vertical
X1: 17.734475MHZ; Crystal_SMD_HC49-SD; DigiKey 300-6138-1-ND

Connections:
+5V: C2.1, C3.1, C4.1, C5.1, U1.4 (AVCC), U1.5 (CE), U1.14 (DVCC), U1.15 (VSYNC), U2.2
/Audio: U2.3
/Bin: C8.1, R3.1, U2.5
/COMPout: J3.1 (In), R5.2, U2.1
/CSYNC: U1.16 (HSYNC), U2.8
/Gin: C7.1, R2.1, U2.6
/Rin: C6.1, R1.1, U2.7
GND: C1.2, C2.2, C3.2, C4.2, C5.2, C11.1, D1.3 (K), J3.2 (Ext), L1.1, MH1.1, MH2.1, MH3.1, MH4.1, R1.2, R2.2, R3.2, R4.1, U1.1 (NTSC/PAL), U1.2 (AGND), U1.12 (TRAP), U1.13 (DGND), U2.4, X1.1
unnamed: C9.2, R5.1
unnamed: C10.1, C11.2, L1.2
unnamed: C10.2, D1.1 (A), R4.2
unnamed: C1.1, U1.3 (4FSC_CLK), X1.2
unnamed: C8.2, U1.8 (BLUE)
unnamed: C9.1, U1.10 (CVBS_OUT)
unnamed: C7.2, U1.7 (GREEN)
unnamed: C6.2, U1.6 (RED)

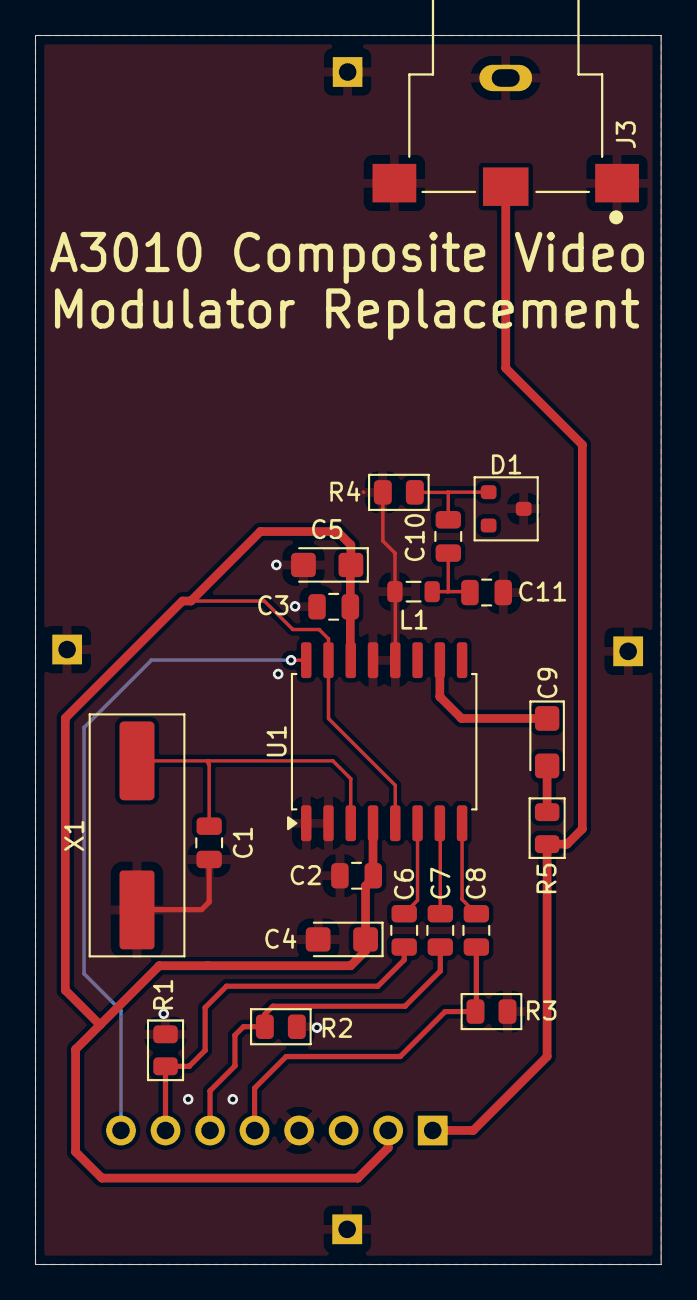
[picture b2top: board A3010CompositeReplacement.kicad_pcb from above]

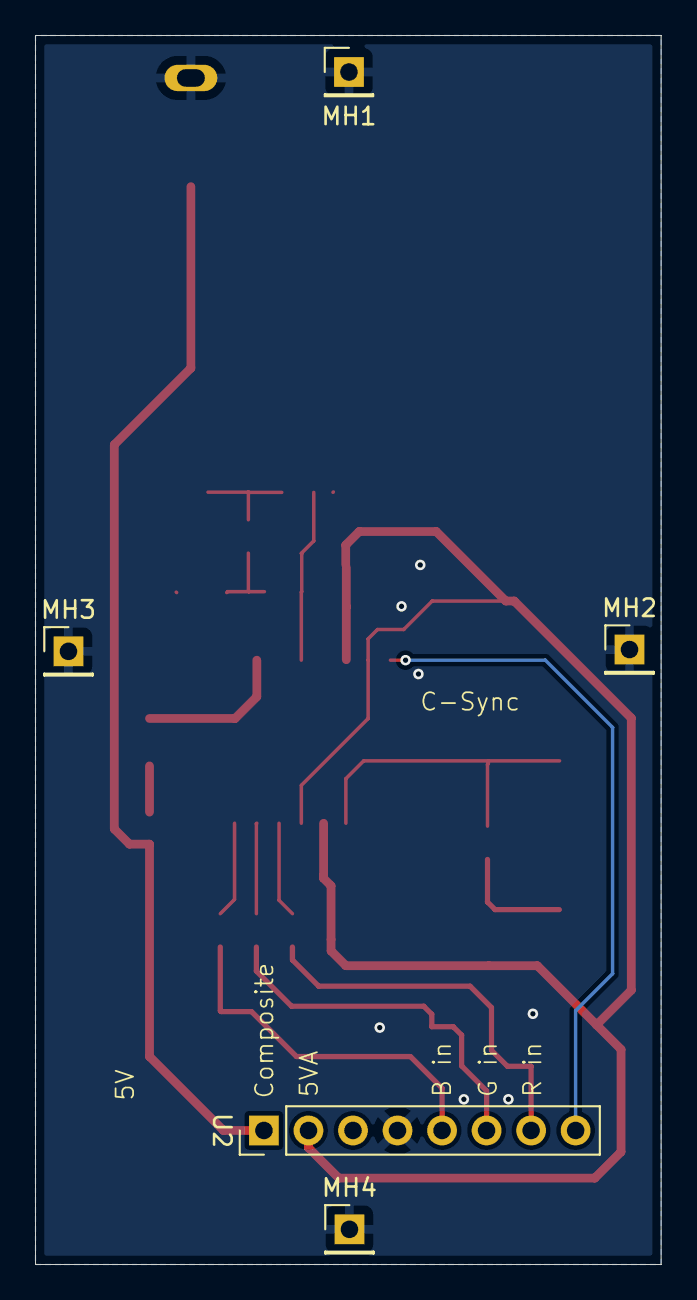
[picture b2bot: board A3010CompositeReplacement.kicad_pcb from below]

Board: 2 copper layers, 35.7 x 70.1 mm, 26 parts (5 on the bottom side), 15 nets.

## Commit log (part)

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2024-12-15 push initial work to git
2024-12-15 add basic readme
2024-12-15 fix render in readme
2024-12-16 add io details
2024-12-17 extend io schematic
2024-12-19 progress schematic
2024-12-20 add vcc clean filter
2024-12-21 add cheeky mean well power swap
2024-12-21 fix port reference locations and lock components
2024-12-22 fix perimter port positions
2024-12-22 remove completely unnecessary -5V rail
2024-12-22 work on io circuits
2024-12-24 data path routing
2024-12-24 update renders
2024-12-24 add digital video schematic
2024-12-25 add rf video output
2024-12-27 more routing
2024-12-27 revise video layout
2024-12-28 wire in LA bus
2024-12-31 tracing refinement
2025-01-02 implement video routing
2025-01-03 video and keyboard routing
2025-01-06 keyboard and joystick routing
2025-01-06 fix rp11
2025-01-08 more traces
2025-01-09 yet more traces
2025-01-10 keyboard routing
2025-01-15 progress power and keyboard
2025-01-15 analogue video
2025-01-17 more analogue video work
2025-01-20 route out SW1 and SW2 traces
2025-01-20 sw trace routing
2025-01-21 last 20 traces to do
2025-01-24 all connections made - almost
2025-01-24 add missing capacitors
2025-01-24 update ibom
2025-01-25 prepare board for beta release
2025-02-01 Update design to remove the use of blind/buried vias to facilitate production
2025-02-23 correct ROM symbol
2025-03-05 fix footprint sizes
2025-03-05 enlarge J-leg footprints
2025-03-05 board layout cosmetics
2025-03-07 adjust shielding perimeter trace and mounting holes
2025-04-24 Update readme with progress
2026-05-15 add ide and rework onboard ram
2026-05-15 complete routing
